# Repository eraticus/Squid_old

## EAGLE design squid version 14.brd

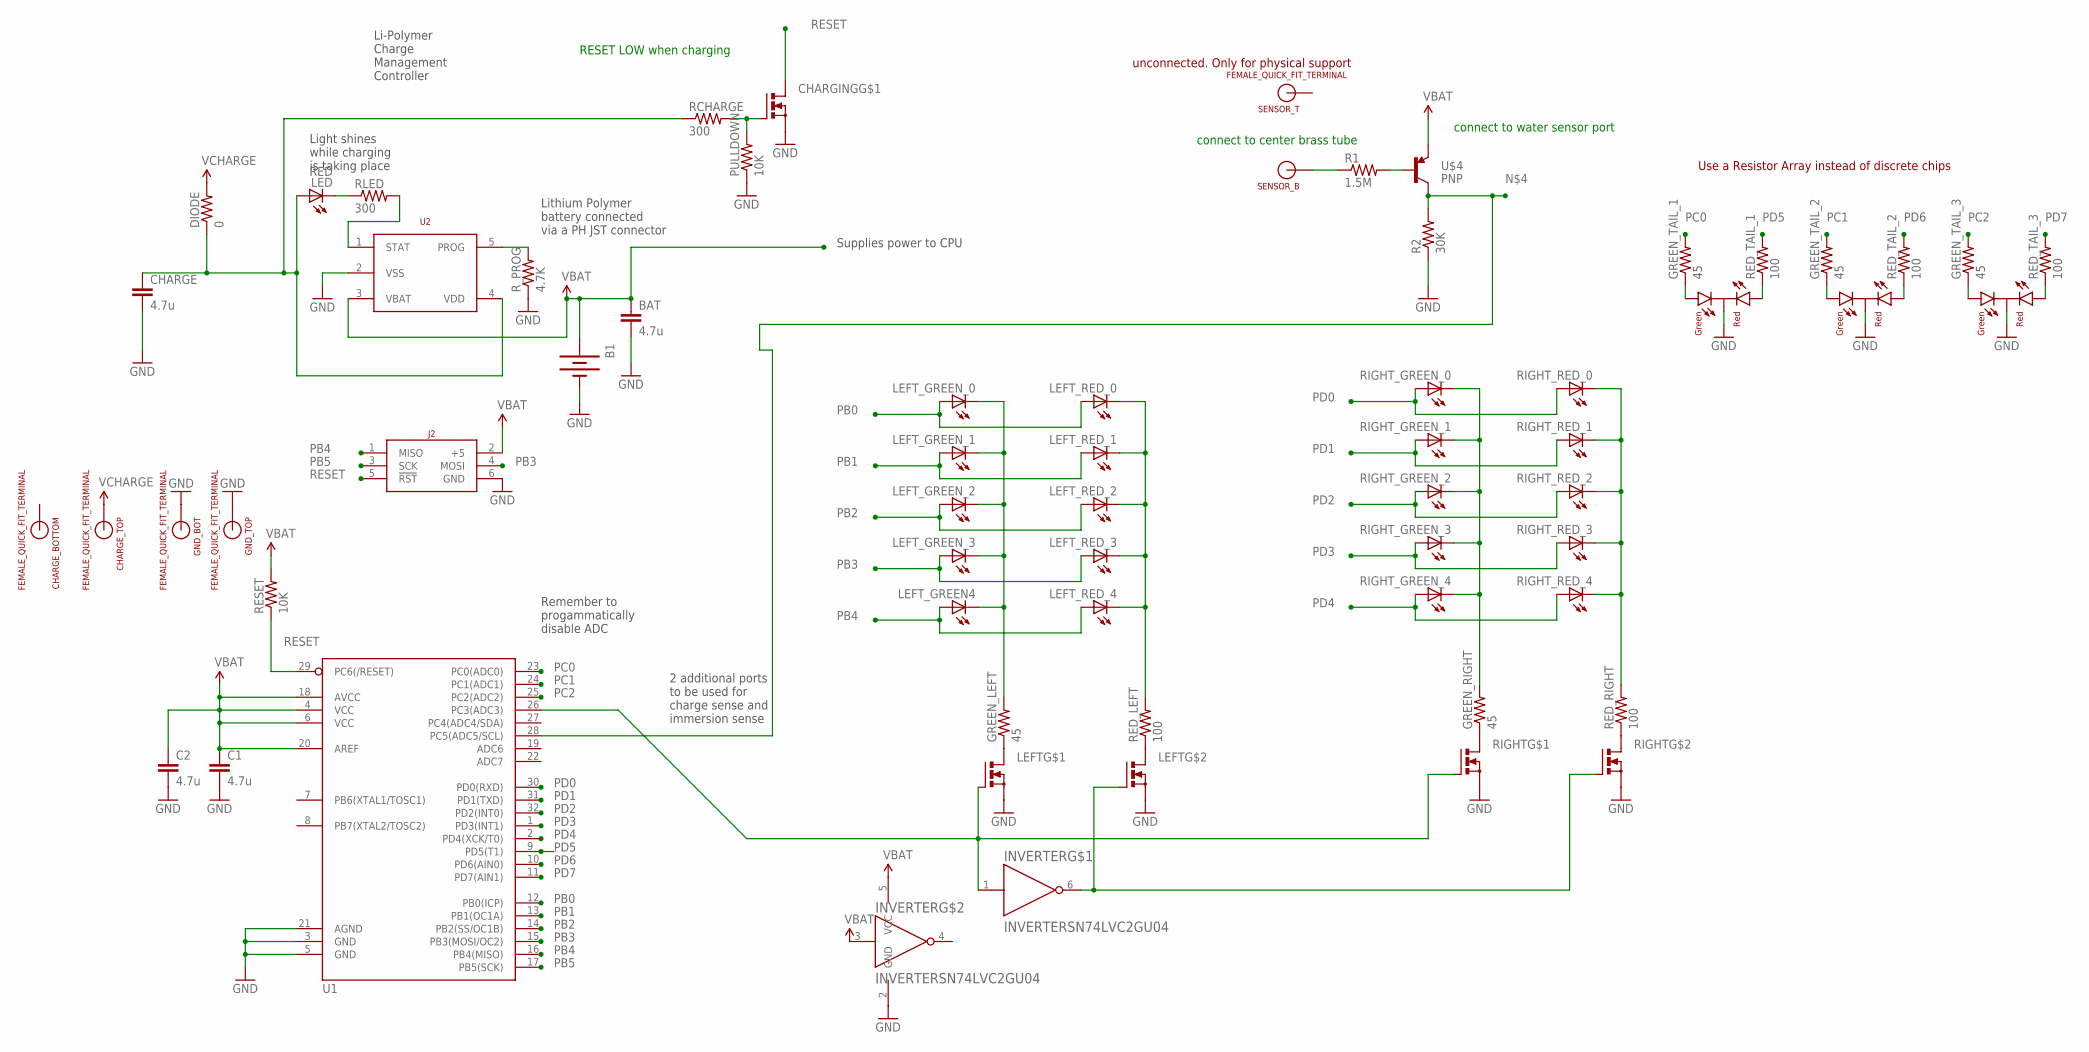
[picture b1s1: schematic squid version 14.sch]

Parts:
B1: COIN_CELL_BATTERYJST; JST_SM
BAT: 4.7u; 1206
C1, C2: 4.7u; 1206
CENTER: LED_RED_GREEN_CC; LED_KINGBRIGHT_BICOLOR_INDICATOR_LAMP
CHARGE: 4.7u; 1206
CHARGE_BOTTOM: FEMALE_QUICK_FIT_TERMINAL; HORIZONTAL_QUICK_CONNECT_3547
CHARGE_TOP: FEMALE_QUICK_FIT_TERMINAL; HORIZONTAL_QUICK_CONNECT_3547
CHARGING: MOSFET_N_DUAL; SOT-23-6
DIODE: 0; 0805
GND_BOT: FEMALE_QUICK_FIT_TERMINAL; HORIZONTAL_QUICK_CONNECT_3547
GND_TOP: FEMALE_QUICK_FIT_TERMINAL; HORIZONTAL_QUICK_CONNECT_3547
GREEN_LEFT: 45; 0805
GREEN_RIGHT: 45; 0805
GREEN_TAIL_1, GREEN_TAIL_2, GREEN_TAIL_3: 45; 0805
INVERTER: INVERTERSN74LVC2GU04; SOT-23-6
J2: ATMEL_PROGRAMMER_HEADERNL; TC2030-INC-NL
LED: RED; CHIP-LED0805
LEFT: MOSFET_N_DUAL; SOT-23-6
LEFT_GREEN4: LEDPLCC2; BIVAR_2-PLCC
LEFT_GREEN_0, LEFT_GREEN_1, LEFT_GREEN_2, LEFT_GREEN_3: LEDPLCC2; BIVAR_2-PLCC
LEFT_RED_0, LEFT_RED_1, LEFT_RED_2, LEFT_RED_3, LEFT_RED_4: LEDPLCC2; BIVAR_2-PLCC
PULLDOWN: 10K; 0805
R1: 1.5M; 0805
R2: 30K; 0805
RCHARGE: 300; 0805
RED_LEFT: 100; 0805
RED_RIGHT: 100; 0805
RED_TAIL_1, RED_TAIL_2, RED_TAIL_3: 100; 0805
RESET: 10K; 0805
RIGHT: MOSFET_N_DUAL; SOT-23-6
RIGHT_GREEN_0, RIGHT_GREEN_1, RIGHT_GREEN_2, RIGHT_GREEN_3, RIGHT_GREEN_4: LEDPLCC2; BIVAR_2-PLCC
RIGHT_RED_0, RIGHT_RED_1, RIGHT_RED_2, RIGHT_RED_3, RIGHT_RED_4: LEDPLCC2; BIVAR_2-PLCC
RLED: 300; 0805
R_PROG: 4.7K; 0805
SENSOR_B: FEMALE_QUICK_FIT_TERMINAL; HORIZONTAL_QUICK_CONNECT_3547
SENSOR_T: FEMALE_QUICK_FIT_TERMINAL; HORIZONTAL_QUICK_CONNECT_3547
U1: ATMEGA328_SMT; TQFP32-08
U2: MCP73832; SOT-23(OT)5_LEAD
U$4: PNP; SOT-23
U$7, U$13: LED_RED_GREEN_CC; LED_KINGBRIGHT_BICOLOR_INDICATOR_LAMP

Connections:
GND: B1.GND (-), BAT.2, C1.2, C2.2, CENTER.2 (C), CHARGE.2, CHARGING.4 (S), GND_BOT.1, GND_TOP.1, INVERTER.2 (GND), J2.6 (GND), LEFT.1 (S), LEFT.4 (S), PULLDOWN.1, R2.1, RIGHT.1 (S), RIGHT.4 (S), R_PROG.1, U1.3 (GND), U1.5 (GND), U1.21 (AGND), U2.2 (VSS), U$7.2 (C), U$13.2 (C)
GREEN_LEFT_CATHODE: GREEN_LEFT.2, LEFT_GREEN4.C, LEFT_GREEN_0.C, LEFT_GREEN_1.C, LEFT_GREEN_2.C, LEFT_GREEN_3.C
unnamed: R1.2, U$4.1 (B)
unnamed: INVERTER.6 (Y), LEFT.2 (G), RIGHT.2 (G)
unnamed: CHARGING.5 (G), PULLDOWN.2, RCHARGE.2
unnamed: R2.2, U1.28 (PC5(ADC5/SCL)), U$4.3 (C)
unnamed: GREEN_LEFT.1, LEFT.3 (D)
unnamed: LEFT.6 (D), RED_LEFT.1
unnamed: INVERTER.1 (A), LEFT.5 (G), RIGHT.5 (G), U1.26 (PC3(ADC3))
unnamed: GREEN_RIGHT.1, RIGHT.3 (D)
unnamed: R1.1, SENSOR_B.1
unnamed: RED_RIGHT.1, RIGHT.6 (D)
unnamed: GREEN_RIGHT.2, RIGHT_GREEN_0.C, RIGHT_GREEN_1.C, RIGHT_GREEN_2.C, RIGHT_GREEN_3.C, RIGHT_GREEN_4.C
unnamed: RED_RIGHT.2, RIGHT_RED_0.C, RIGHT_RED_1.C, RIGHT_RED_2.C, RIGHT_RED_3.C, RIGHT_RED_4.C
unnamed: LED.C, RLED.1
unnamed: R_PROG.2, U2.5 (PROG)
unnamed: GREEN_TAIL_1.1, U$7.3 (GREEN)
unnamed: CENTER.3 (GREEN), GREEN_TAIL_2.1
unnamed: CHARGE.1, DIODE.1, LED.A, RCHARGE.1, U2.4 (VDD)
unnamed: GREEN_TAIL_3.1, U$13.3 (GREEN)
unnamed: RED_TAIL_1.1, U$7.1 (RED)
unnamed: CENTER.1 (RED), RED_TAIL_2.1
unnamed: RED_TAIL_3.1, U$13.1 (RED)
PB0: LEFT_GREEN_0.A, LEFT_RED_0.A, U1.12 (PB0(ICP))
PB1: LEFT_GREEN_1.A, LEFT_RED_1.A, U1.13 (PB1(OC1A))
PB2: LEFT_GREEN_2.A, LEFT_RED_2.A, U1.14 (PB2(SS/OC1B))
PB3: J2.4 (MOSI), LEFT_GREEN_3.A, LEFT_RED_3.A, U1.15 (PB3(MOSI/OC2))
PB4: J2.1 (MISO), LEFT_GREEN4.A, LEFT_RED_4.A, U1.16 (PB4(MISO))
PB5: J2.3 (SCK), U1.17 (PB5(SCK))
PC0: GREEN_TAIL_1.2, U1.23 (PC0(ADC0))
PC1: GREEN_TAIL_2.2, U1.24 (PC1(ADC1))
PC2: GREEN_TAIL_3.2, U1.25 (PC2(ADC2))
PD0: RIGHT_GREEN_0.A, RIGHT_RED_0.A, U1.30 (PD0(RXD))
PD1: RIGHT_GREEN_1.A, RIGHT_RED_1.A, U1.31 (PD1(TXD))
PD2: RIGHT_GREEN_2.A, RIGHT_RED_2.A, U1.32 (PD2(INT0))
PD3: RIGHT_GREEN_3.A, RIGHT_RED_3.A, U1.1 (PD3(INT1))
PD4: RIGHT_GREEN_4.A, RIGHT_RED_4.A, U1.2 (PD4(XCK/T0))
PD5: RED_TAIL_1.2, U1.9 (PD5(T1))
PD6: RED_TAIL_2.2, U1.10 (PD6(AIN0))
PD7: RED_TAIL_3.2, U1.11 (PD7(AIN1))
RED_LEFT_CATHODE: LEFT_RED_0.C, LEFT_RED_1.C, LEFT_RED_2.C, LEFT_RED_3.C, LEFT_RED_4.C, RED_LEFT.2
RESET: CHARGING.3 (D), J2.5 (!RST!), RESET.1, U1.29 (PC6(/RESET))
STAT: RLED.2, U2.1 (STAT)
VBAT: B1.VCC (+), BAT.1, C1.1, C2.1, INVERTER.3 (A), INVERTER.5 (VCC), J2.2 (+5), RESET.2, U1.4 (VCC), U1.6 (VCC), U1.18 (AVCC), U1.20 (AREF), U2.3 (VBAT), U$4.2 (E)
VCHARGE: CHARGE_TOP.1, DIODE.2

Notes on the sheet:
2 additional ports to be used for charge sense and immersion sense
Lithium Polymer battery connected via a PH JST connector
Light shines while charging is taking place
Supplies power to CPU
Li-Polymer Charge Management Controller
Remember to progammatically disable ADC
connect to center brass tube
connect to water sensor port
RESET LOW when charging
Use a Resistor Array instead of discrete chips
unconnected. Only for physical support

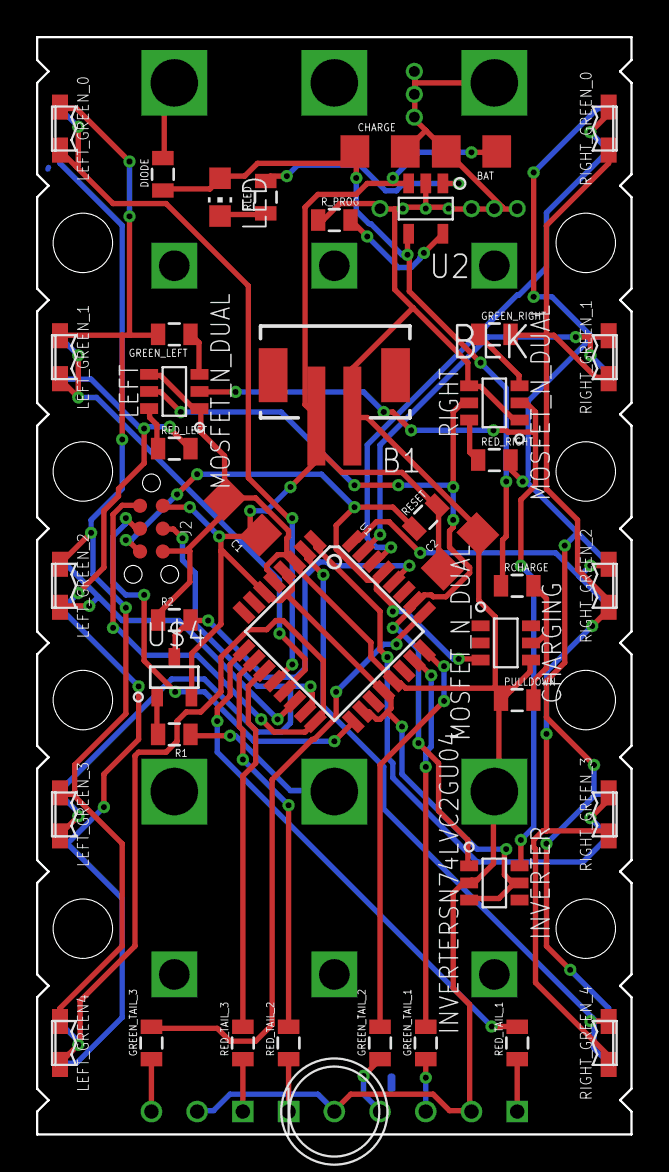
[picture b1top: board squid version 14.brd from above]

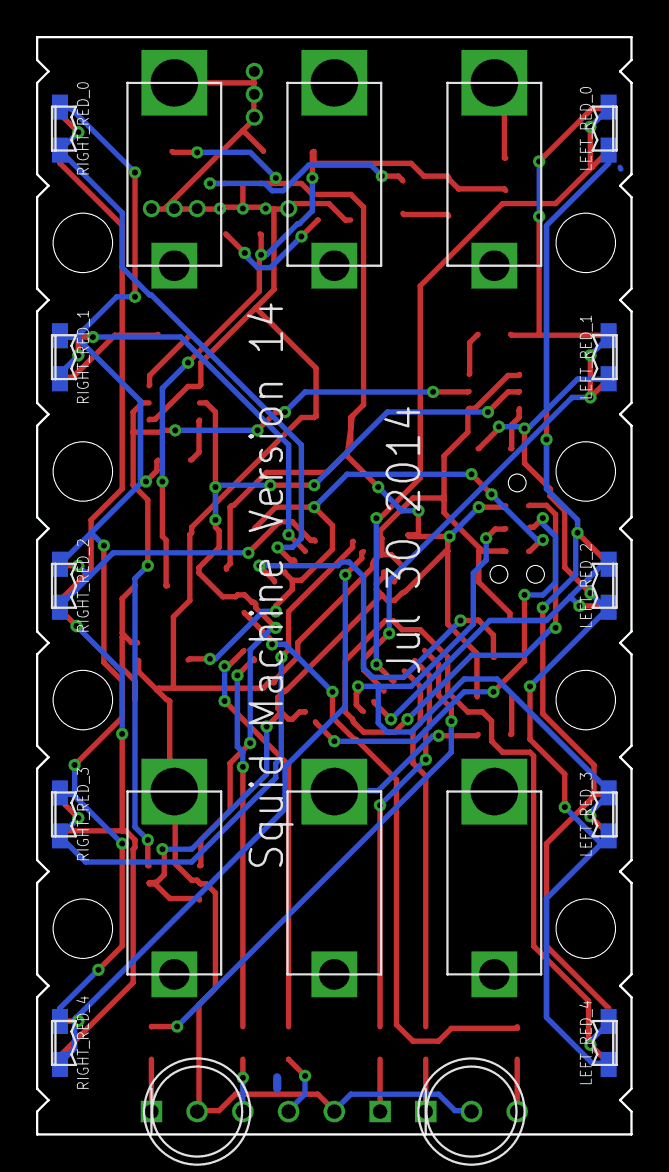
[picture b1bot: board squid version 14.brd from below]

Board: 2 copper layers, 33.0 x 61.0 mm, 62 parts (18 on the bottom side), 45 nets.

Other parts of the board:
U$12: SQUID_14

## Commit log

2014-07-30 Initial commit of Squid project
    Includes schematic, board, and program
2014-07-30 Integrate D5,D6 and D7 ports into tail light code
2014-07-30 corret gitignore
2014-07-31 add backup files
2014-07-31 small test change
2014-07-31 put RG TH lights in rear
    Rearranged board to hold TH parts in rear.
2014-07-31 add label
    minor change
2014-07-31 added some comments
2014-08-01 disconnect top center tube holder
    Does not need an electrical connection
2014-08-03 RED and GREEN tail lights code
    RED and GREEN tail lights turned on and off properly
2014-09-05 assign values of ballast resistors
    Put proper values of ballast resistors into schematic
2014-09-05 reverse lateral light display
    change direction of lateral light display from head to tail, to tail to
    head
2014-09-09 change speed and direction of lights
    Lights sped up, and reversed. Tail lights make clockwise pattern
    instead of back and forth
2014-09-12 correct current programming resistor value
    Major mistake in current programming resistor!! Changed from 24 to
    4.7K!!!
2014-09-12 new file?

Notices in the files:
parts and their libraries:
SparkFun-DigitalIC: Licensing: CC v3.0 Share-Alike You are welcome to use this library for commercial purposes.
